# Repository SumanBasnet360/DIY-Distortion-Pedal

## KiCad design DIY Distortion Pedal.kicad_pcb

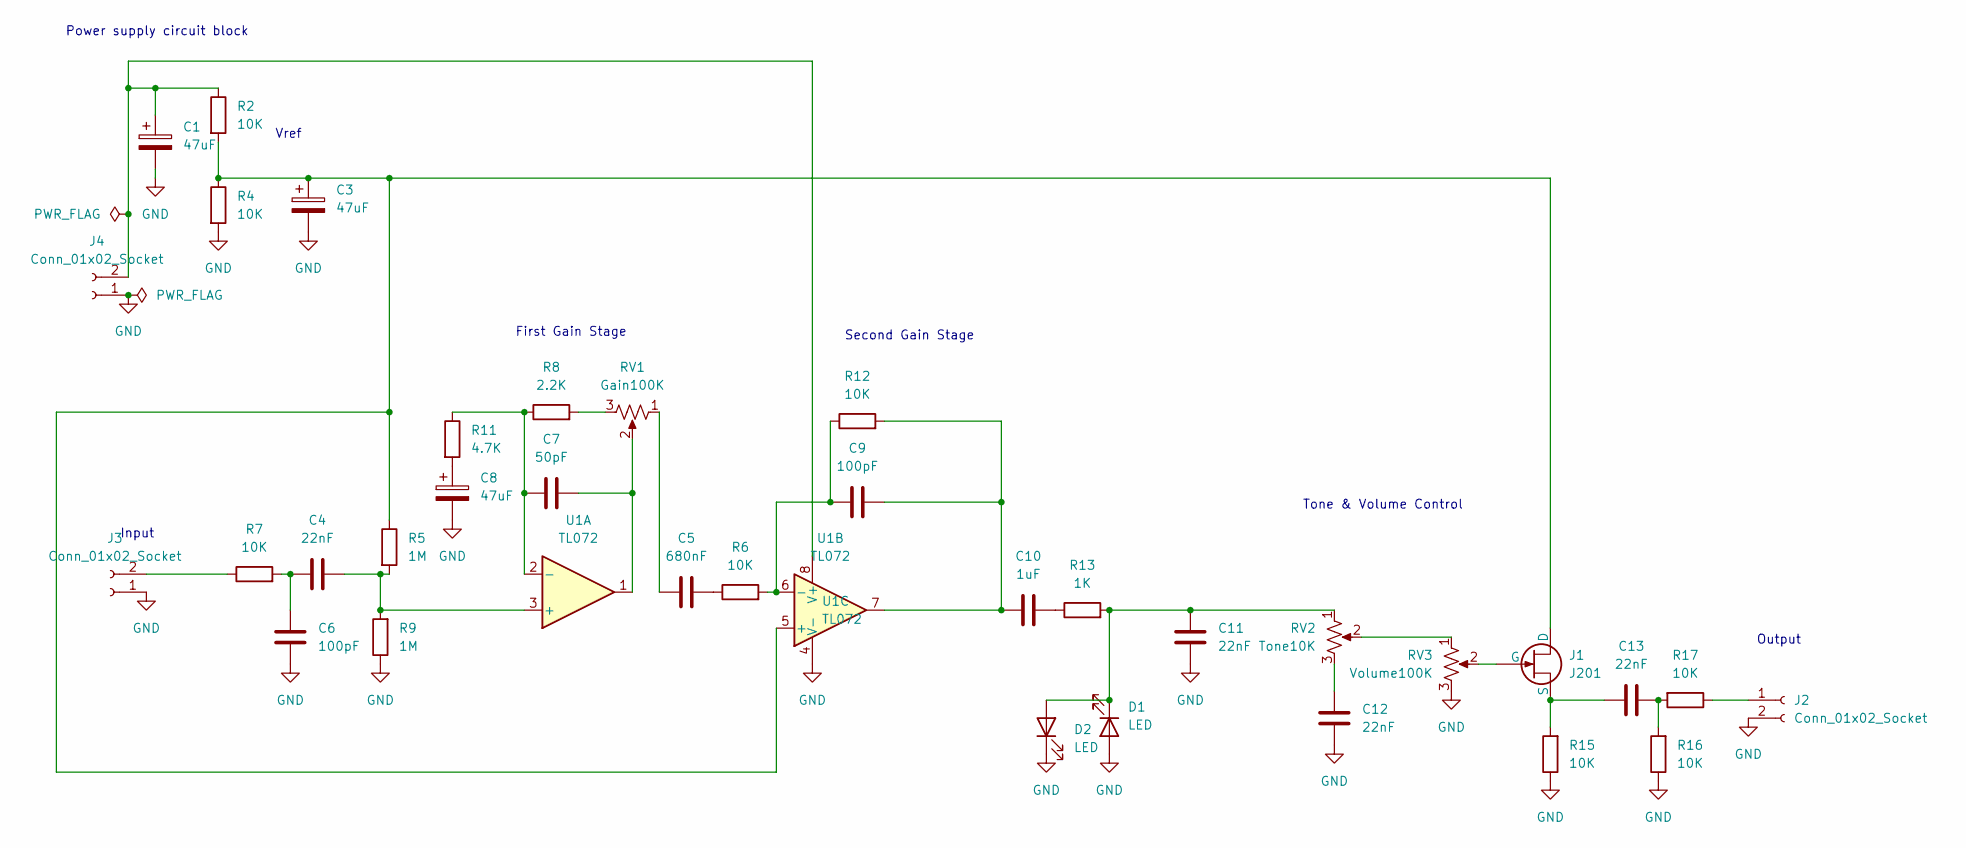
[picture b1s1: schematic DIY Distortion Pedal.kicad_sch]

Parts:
C1, C3: 47uF; CP_Radial_D4.0mm_P2.00mm
C4, C11, C12, C13: 22nF; C_Disc_D4.7mm_W2.5mm_P5.00mm
C5: 680nF; C_Disc_D4.7mm_W2.5mm_P5.00mm
C6, C9: 100pF; C_Disc_D4.7mm_W2.5mm_P5.00mm
C7: 50pF; C_Disc_D4.7mm_W2.5mm_P5.00mm
C8: 47uF; C_Disc_D4.7mm_W2.5mm_P5.00mm
C10: 1uF; C_Disc_D4.7mm_W2.5mm_P5.00mm
D1, D2: LED; LED_D5.0mm
J1: J201; TO-92
J2, J3, J4: Conn_01x02_Socket; TerminalBlock_bornier-2_P5.08mm
R2, R4, R6, R7, R12, R15, R16, R17: 10K; R_Axial_DIN0207_L6.3mm_D2.5mm_P7.62mm_Horizontal
R5, R9: 1M; R_Axial_DIN0207_L6.3mm_D2.5mm_P7.62mm_Horizontal
R8: 2.2K; R_Axial_DIN0207_L6.3mm_D2.5mm_P7.62mm_Horizontal
R11: 4.7K; R_Axial_DIN0207_L6.3mm_D2.5mm_P7.62mm_Horizontal
R13: 1K; R_Axial_DIN0207_L6.3mm_D2.5mm_P7.62mm_Horizontal
RV1: Gain100K; Potentiometer_Bourns_3386C_Horizontal
RV2: Tone10K; Potentiometer_Bourns_3386C_Horizontal
RV3: Volume100K; Potentiometer_Bourns_3386C_Horizontal
U1: TL072; DIP-8_W7.62mm

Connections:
GND: C1.2, C3.2, C6.1, C8.2, C11.1, C12.1, D1.2 (A), D2.1 (K), J2.2, J3.1, J4.1, R4.2, R9.1, R15.1, R16.1, RV3.3, U1.4 (V-)
unnamed: C4.1, C6.2, R7.2
unnamed: C5.1, R6.1
unnamed: C5.2, RV1.1
unnamed: C7.1, RV1.2, U1.1
unnamed: C8.1, R11.2
unnamed: C10.1, R13.1
unnamed: C9.1, C10.2, R12.2, U1.7
unnamed: C12.2, RV2.3
unnamed: C13.1, R16.2, R17.2
unnamed: C11.2, D1.1 (K), D2.2 (A), R13.2, RV2.1
unnamed: C3.1, J1.1 (D), R2.2, R4.1, R5.1, U1.5 (+)
unnamed: J1.2 (G), RV3.2
unnamed: C13.2, J1.3 (S), R15.2
unnamed: J2.1, R17.1
unnamed: J3.2, R7.1
unnamed: C1.1, J4.2, R2.1, U1.8 (V+)
unnamed: R8.2, RV1.3
unnamed: RV2.2, RV3.1
unnamed: C4.2, R5.2, R9.2, U1.3 (+)
unnamed: C7.2, R8.1, R11.1, U1.2 (-)
unnamed: C9.2, R6.2, R12.1, U1.6 (-)

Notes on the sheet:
Vref
Output
Power supply circuit block
Tone & Volume Control
First Gain Stage
Input
Second Gain Stage

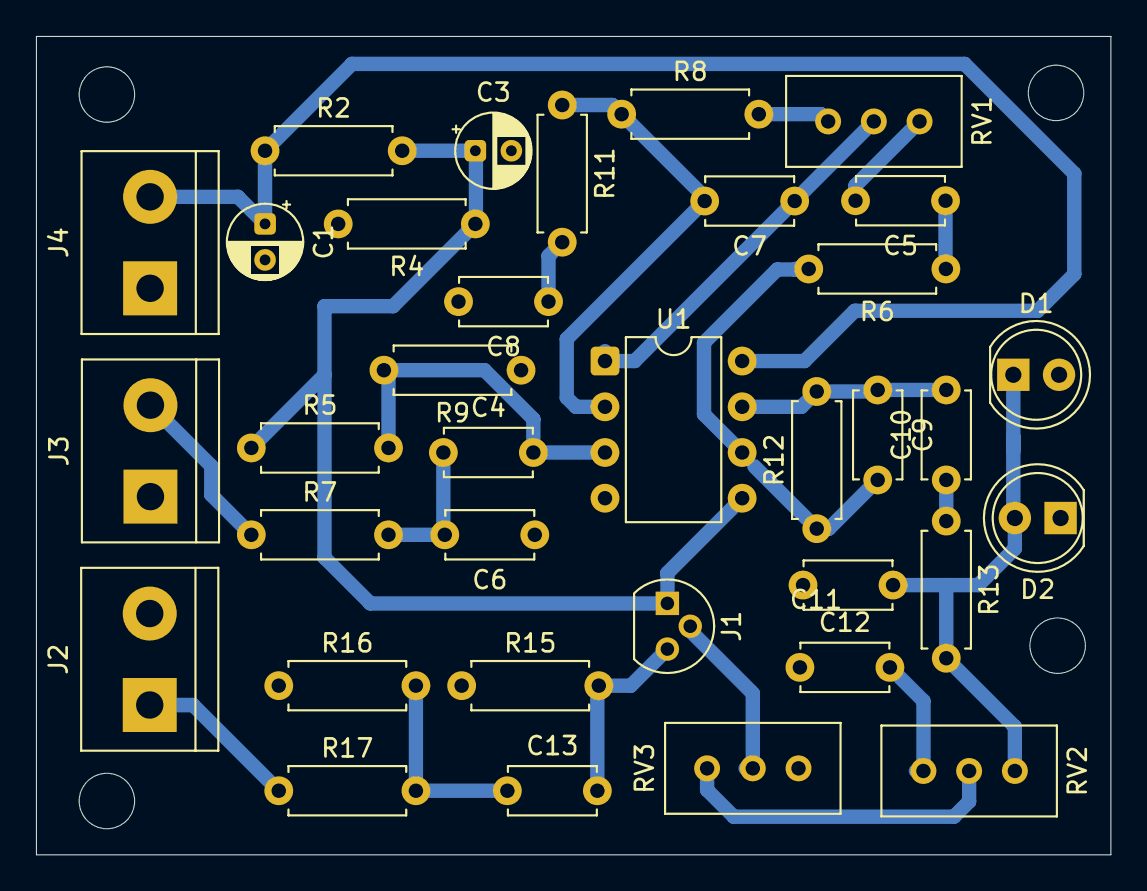
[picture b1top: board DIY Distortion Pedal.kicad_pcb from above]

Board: 2 copper layers, 59.7 x 45.5 mm, 35 parts (0 on the bottom side), 22 nets.

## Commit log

2025-09-09 V1 initial commit
2025-09-14 Removed backup files
2025-09-14 Removed cache files
